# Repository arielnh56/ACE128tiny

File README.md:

# ace128tiny
Porting the ACE128 to the ATtiny841

This is experimental, just me playing with ATTiny chips because they are so cute.

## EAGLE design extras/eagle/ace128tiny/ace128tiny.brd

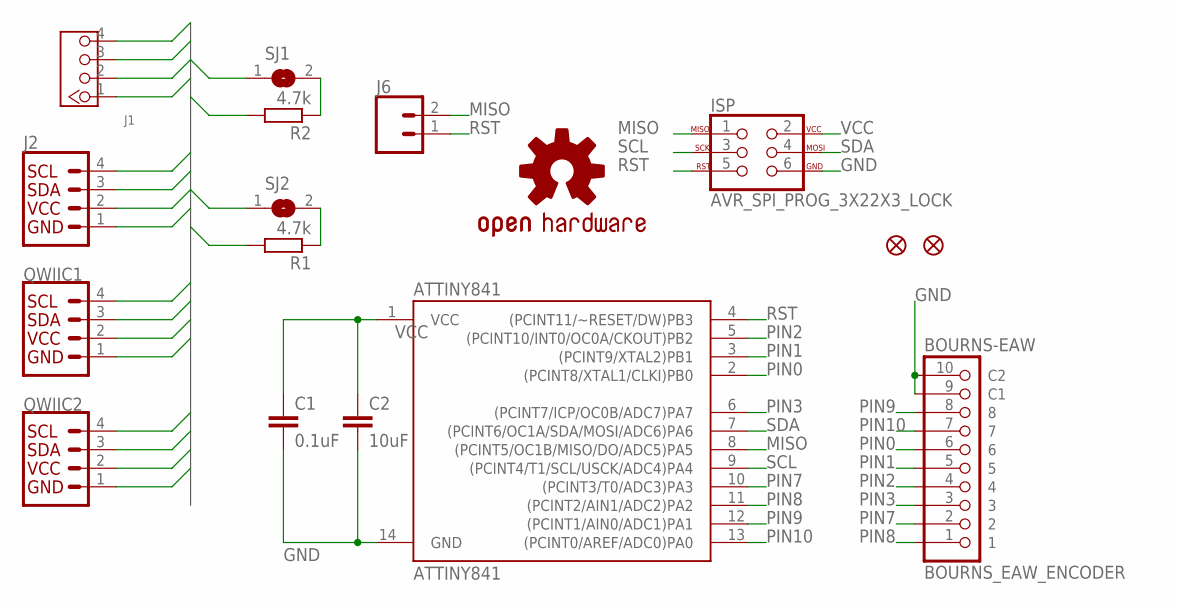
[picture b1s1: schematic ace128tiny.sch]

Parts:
ATTINY841: ATTINY841; SO14
BOURNS_EAW_ENCODER: BOURNS-EAW
C1: 0.1uF; C0603
C2: 10uF; C0805
FD1, FD2: FIDUCIAL1X2; FIDUCIAL-1X2
ISP: AVR_SPI_PROG_3X22X3_LOCK; 2X3_LOCK
J1: GROVE I2C; HW4-2.0-NO-OUTLINE
J2: I2C_STANDARD; 1X04
J6: CONN_02; 1X02
LOGO1: OSHW-LOGOS; OSHW-LOGO-S
QWIIC1, QWIIC2: QWIIC_CONNECTORJS-1MM; 1X04_1MM_RA
R1, R2: 4.7k; R0603
SJ1, SJ2: SJ

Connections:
GND: ATTINY841.14 (GND), BOURNS_EAW_ENCODER.9 (C1), BOURNS_EAW_ENCODER.10 (C2), C1.2, C2.2, ISP.6, J1.4, J2.1, QWIIC1.1 (GND), QWIIC2.1 (GND)
MISO: ATTINY841.8 ((PCINT5/OC1B/MISO/DO/ADC5)PA5), ISP.1, J6.2
unnamed: R2.1, SJ1.2
unnamed: R1.1, SJ2.2
PIN0: ATTINY841.2 ((PCINT8/XTAL1/CLKI)PB0), BOURNS_EAW_ENCODER.6
PIN1: ATTINY841.3 ((PCINT9/XTAL2)PB1), BOURNS_EAW_ENCODER.5
PIN2: ATTINY841.5 ((PCINT10/INT0/OC0A/CKOUT)PB2), BOURNS_EAW_ENCODER.4
PIN3: ATTINY841.6 ((PCINT7/ICP/OC0B/ADC7)PA7), BOURNS_EAW_ENCODER.3
PIN7: ATTINY841.10 ((PCINT3/T0/ADC3)PA3), BOURNS_EAW_ENCODER.2
PIN8: ATTINY841.11 ((PCINT2/AIN1/ADC2)PA2), BOURNS_EAW_ENCODER.1
PIN9: ATTINY841.12 ((PCINT1/AIN0/ADC1)PA1), BOURNS_EAW_ENCODER.8
PIN10: ATTINY841.13 ((PCINT0/AREF/ADC0)PA0), BOURNS_EAW_ENCODER.7
RST: ATTINY841.4 ((PCINT11/~RESET/DW)PB3), ISP.5, J6.1
SCL: ATTINY841.9 ((PCINT4/T1/SCL/USCK/ADC4)PA4), ISP.3, J1.1, J2.4, QWIIC1.4 (SCL), QWIIC2.4 (SCL), SJ1.1
SDA: ATTINY841.7 ((PCINT6/OC1A/SDA/MOSI/ADC6)PA6), ISP.4, J1.2, J2.3, QWIIC1.3 (SDA), QWIIC2.3 (SDA), SJ2.1
VCC: ATTINY841.1 (VCC), C1.1, C2.1, ISP.2, J1.3, J2.2, QWIIC1.2 (VCC), QWIIC2.2 (VCC), R1.2, R2.2

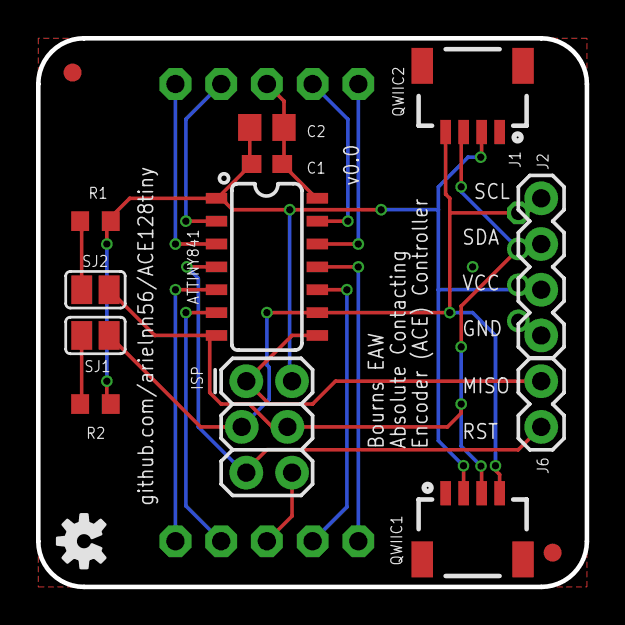
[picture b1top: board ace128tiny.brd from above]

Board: 2 copper layers, 30.5 x 30.5 mm, 17 parts (1 on the bottom side), 16 nets.

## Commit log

2021-04-16 First steps towards a product
    Checking in to rename the project
2021-04-16 Completed rename of tree
    Windows is a PITA
2021-04-19 Base functionality complete
    Getters and setters all done.
    Reworked reverse significantly - may want to punt that over to ACE128
2021-04-22 board design v0.0
    First pass at the board design - oshpark prototypes

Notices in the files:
parts and their libraries:
SparkFun-Aesthetics: Licensing: Creative Commons ShareAlike 4.0 International - https://creativecommons.org/licenses/by-sa/4.0
